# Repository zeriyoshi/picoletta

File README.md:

# picoletta
Jashin-chan Dropkick Open source Tenkey Macropad (formerly JCDK21)

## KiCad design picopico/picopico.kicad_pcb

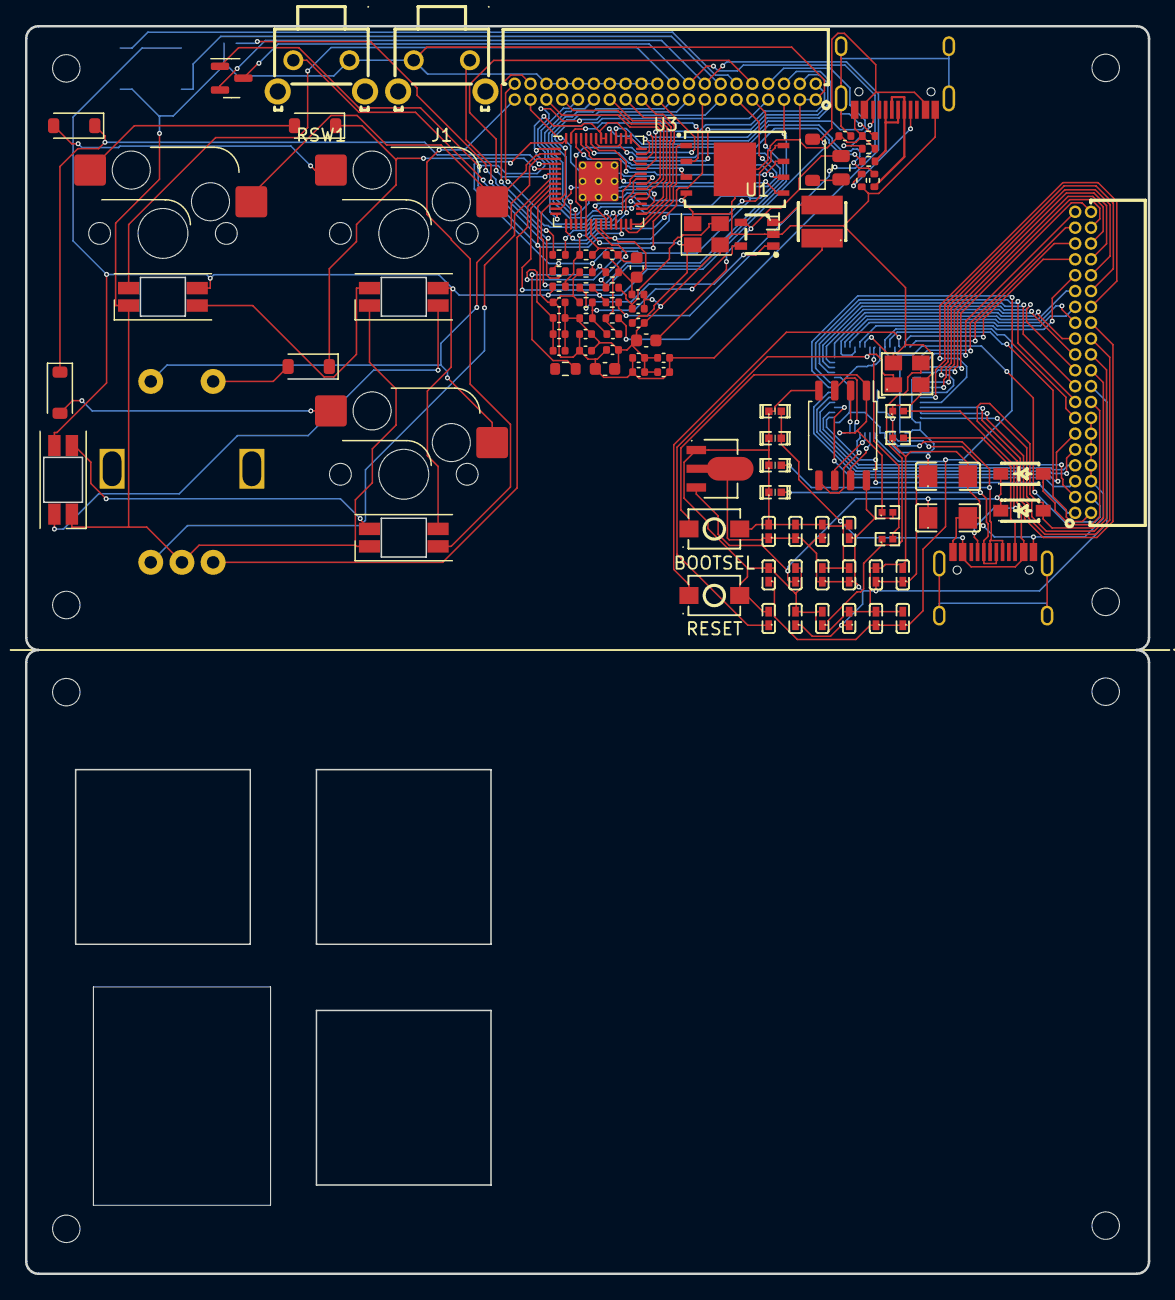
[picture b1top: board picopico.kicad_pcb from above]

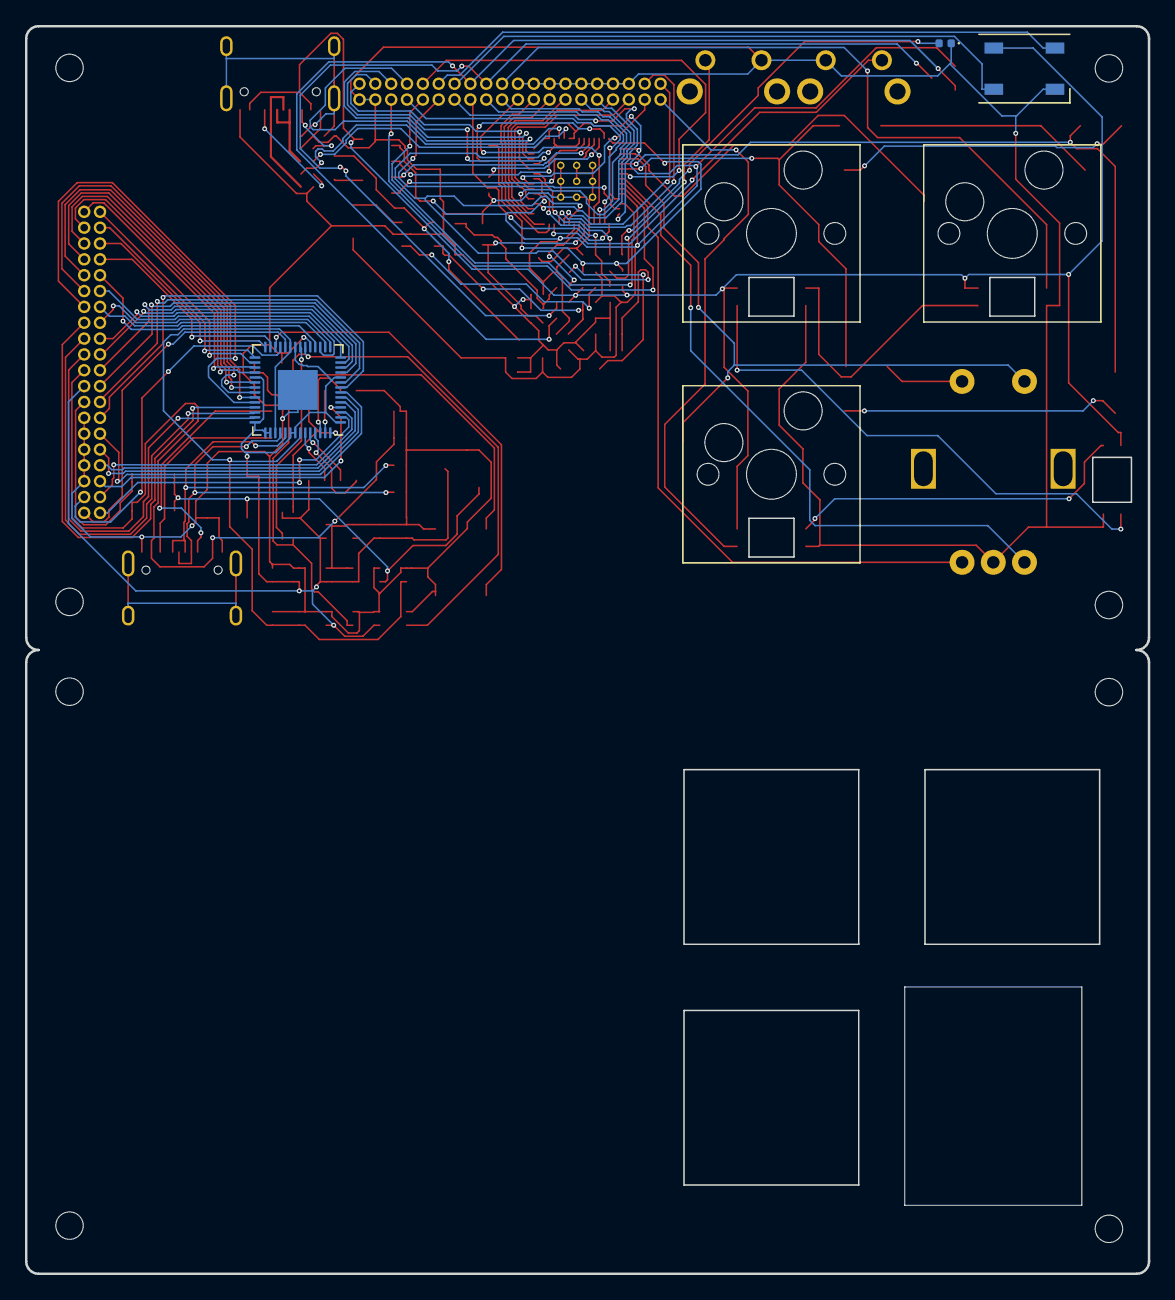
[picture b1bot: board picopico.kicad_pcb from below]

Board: 2 copper layers, 90.0 x 100.0 mm, 114 parts (9 on the bottom side), 125 nets.

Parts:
C1: 0.1uf 0402; C_0402_1005Metric
C2: 10uf 0402; C_0603_1608Metric
C3, C5, C6, C10, C12, C13, C14, C15, C16, C17, C18: 100nf 0402; C_0402_1005Metric
C4, C9: 10uf 0603; C_0603_1608Metric
C7, C11: 1uf 0402; C_0402_1005Metric
C8: 22pF; C_0402_1005Metric
C19, C20: 22pf 0402; C_0402_1005Metric
D1: 1N4002W; D_SOD-123
D2, D3, D4, D5: 1N1418W; D_SOD-123
D6: WS2812B; LED_WS2812B_PLCC4_5.0x5.0mm_P3.2mm
D7, D8, D9, D10: 0402ESDA-05N; D0402-BI
F1: 0805L050WR; Fuse_0805_2012Metric
FLASH1: W25Q16JVUXIQ; SON127P800X600X80-9N
G1, G2: LOGO; zeriparrot
GPIO25_LED1: LED_0402; LED_0402_1005Metric
GPIO25_RESISTOR1: 470 0402; R_0402_1005Metric
H1, H2, H3, H4, H5, H6, H7, H8: MountingHole; MountingHole_2.2mm_M2
H9, H10, H12: Switch_Hole
H11: RotaryEncoder_EC11-Hole
J1: 1-1825027-7; SW-TH_KH-6X6X4.3H-ZJ
L1: SWPA3015S2R2NT; IND-SMD_L3.0-W3.0
LED1, LED2, LED3, LED4: YS-SK6812MINI-E
Q1: BSS138; SOT-23
R1, R2: 5.1K 0402; R_0402_1005Metric
R3: 220 0402; R_0402_1005Metric
R4, R15: 1K 0402; R_0402_1005Metric
R5: 5.6K 0402; R_0402_1005Metric
R6, R7, R16, R17: 10K 0402; R_0402_1005Metric
R8: 100K 0402; R_0402_1005Metric
R9: 680K; R_0402_1005Metric
R10: 150K; R_0402_1005Metric
R11, R12: 27r 0402 resistor; R_0402_1005Metric
R13: 200 0603; R_0603_1608Metric
R14: 1 0402; R_0402_1005Metric
R19, R20: 0402WGF5101TCE; R0402
RSW1: 1-1825027-7; SW-TH_KH-6X6X4.3H-ZJ
SW1, SW2, SW3: SW_PUSH; SW_Hotswap_Kailh_MX_1.00u
SW4: RotaryEncoder_Switch; RotaryEncoder_EC11-Switch
U1: TD6810; SOT-23-5_L3.0-W1.7-P0.95-LS2.8-BR
U2: RP2040; RP2040-QFN-56
U3, U5: X1321FR-2X20-C43D24; CONN-TH_40P_X1321FR-2X20-C43D24
USB1, USB2: TYPE-C-31-M-12; HRO-TYPE-C-31-M-12
XTRAPI_C1, XTRAPI_C3: 0402CG300J500NT; C0402
XTRAPI_C2, XTRAPI_C5, XTRAPI_C6, XTRAPI_C7, XTRAPI_C8, XTRAPI_C9, XTRAPI_C10, XTRAPI_C11, XTRAPI_C12, XTRAPI_C13, XTRAPI_C15, XTRAPI_C16, XTRAPI_C17, XTRAPI_C18: CL05A106MQ5NUNC; C0402
XTRAPI_C4, XTRAPI_C14: CL31A107MQHNNNE; C1206
XTRAPI_R2: 0402WGF1002TCE; R0402
XTRAPI_R4: 0402WGF1001TCE; R0402
XTRAPI_U2: W25Q128JVS; SOIC-8_5.23x5.23mm_P1.27mm
XTRAPI_U3: RP2040; QFN-56-1EP_7x7mm_P0.4mm_EP3.2x3.2mm
XTRAPI_U4: AZ1117R-3_3TRE1; SOT-89-3_L4.5-W2.5-P1.50-LS4.2-BR
XTRAPI_U6, XTRAPI_U7: B5819W_C8598; SOD-123_L2.7-W1.6-LS3.7-RD-1
XTRAPI_X1: X322512MSB4SI; OSC-SMD_4P-L3.2-W2.5-BL
XTRA_SW_BOOTSEL1: TSA343G00-250J2; SW-SMD_L4.0-W2.9-LS5.0
XTRA_SW_RESET1: TSA343G00-250J2; SW-SMD_L4.0-W2.9-LS5.0
Y1: 3225_4P; Crystal_SMD_3225-4Pin_3.2x2.5mm

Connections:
3V3_EN: R8.1, U1.1 (RUN)
+1V1: C5.1, C6.1, C7.1, U2.23 (DVDD), U2.45 (VREG_VOUT), U2.50 (DVDD)
+3V3: C2.1, C3.1, C8.2, C9.1, C10.1, C11.1, C12.1, C13.1, C14.1, C15.1, C16.1, C17.1, C18.1, FLASH1.8 (VCC), L1.2, Q1.1 (G), R7.1, R9.1, R14.2, R17.1, U2.1 (IOVDD), U2.10 (IOVDD), U2.22 (IOVDD), U2.33 (IOVDD), U2.42 (IOVDD), U2.43 (ADC_AVDD), U2.44 (VREG_IN), U2.48 (USB_VDD), U2.49 (IOVDD)
/ADC_VREF: R13.2, R14.1
/D+: R11.2, U2.47 (USB_DP)
/D-: R12.2, U2.46 (USB_DM)
/GPIO7: U2.9 (GPIO7), U3.5
/GPIO8: U2.11 (GPIO8), U3.7
/GPIO9: U2.12 (GPIO9), U3.9
/GPIO10: U2.13 (GPIO10), U3.11
/GPIO11: U2.14 (GPIO11), U3.13
/GPIO12: U2.15 (GPIO12), U3.15
/GPIO13: U2.16 (GPIO13), U3.17
/GPIO14: U2.17 (GPIO14), U3.19
/GPIO15: U2.18 (GPIO15), U3.21
/GPIO16: U2.27 (GPIO16), U3.23
/GPIO17: U2.28 (GPIO17), U3.25
/GPIO18: U2.29 (GPIO18), U3.27
/GPIO19: U2.30 (GPIO19), U3.29
/GPIO20: U2.31 (GPIO20), U3.31
/GPIO21: U2.32 (GPIO21), U3.33
/GPIO22: U2.34 (GPIO22), U3.35
/GPIO23: U2.35 (GPIO23), U3.37
/GPIO24: R5.2, R6.1, U2.36 (GPIO24)
/GPIO25: GPIO25_RESISTOR1.2, U2.37 (GPIO25)
/GPIO26_ADC0: U2.38 (GPIO26_ADC0), U3.2
/GPIO27_ADC1: U2.39 (GPIO27_ADC1), U3.4
/GPIO28_ADC2: U2.40 (GPIO28_ADC2), U3.6
/GPIO29_ADC3: U2.41 (GPIO29_ADC3), U3.8
/QSPI_SCLK: FLASH1.6 (CLK), U2.52 (QSPI_SCLK)
/QSPI_SD0: FLASH1.5 (DI(IO0)), U2.53 (QSPI_SD0)
/QSPI_SD1: FLASH1.2 (DO(IO1)), U2.55 (QSPI_SD1)
/QSPI_SD2: FLASH1.3 (IO2), U2.54 (QSPI_SD2)
/QSPI_SD3: FLASH1.7 (IO3), U2.51 (QSPI_SD3)
/QSPI_SS: FLASH1.1 (~CS), R4.1, R7.2, U2.56 (QSPI_SS)
/RGB0: U2.6 (GPIO4), U3.10
/RGB0IN: LED1.4 (DIN), U3.20
/RGB0MOSFETIN: Q1.2 (S), R17.2, U3.16
/RGB0MOSFETOUT: Q1.3 (D), R16.2, U3.18
/RGB0OUT: LED4.2 (DOUT), U3.39
/RGB0WSIN: D6.4 (DIN), U3.12
/RGB0WSOUT: D6.2 (DOUT), U3.14
/RUN: RSW1.2, U2.26 (RUN)
/SWCLK: U2.24 (SWCLK), U3.40
/SWD: U2.25 (SWD), U3.38
/XP_+3V3: U5.18, XTRAPI_C2.1, XTRAPI_C4.1, XTRAPI_C5.1, XTRAPI_C10.1, XTRAPI_C11.1, XTRAPI_C12.1, XTRAPI_C13.1, XTRAPI_C15.1, XTRAPI_C16.1, XTRAPI_C17.1, XTRAPI_C18.1, XTRAPI_R2.2, XTRAPI_U2.8 (VCC), XTRAPI_U3.1 (IOVDD), XTRAPI_U3.10 (IOVDD), XTRAPI_U3.22 (IOVDD), XTRAPI_U3.33 (IOVDD), XTRAPI_U3.42 (IOVDD), XTRAPI_U3.43 (ADC_AVDD), XTRAPI_U3.44 (VREG_IN), XTRAPI_U3.48 (USB_VDD), XTRAPI_U3.49 (IOVDD), XTRAPI_U4.2 (OUTPUT)
/XP_BOOTSEL: XTRAPI_R2.1, XTRAPI_U2.1 (~CS), XTRAPI_U3.56 (QSPI_SS), XTRA_SW_BOOTSEL1.1
/XP_GPIO0: U5.1, XTRAPI_U3.2 (GPIO0)
/XP_GPIO1: U5.3, XTRAPI_U3.3 (GPIO1)
/XP_GPIO2: U5.5, XTRAPI_U3.4 (GPIO2)
/XP_GPIO3: U5.7, XTRAPI_U3.5 (GPIO3)
/XP_GPIO4: U5.9, XTRAPI_U3.6 (GPIO4)
/XP_GPIO5: U5.11, XTRAPI_U3.7 (GPIO5)
/XP_GPIO6: U5.13, XTRAPI_U3.8 (GPIO6)
/XP_GPIO7: U5.15, XTRAPI_U3.9 (GPIO7)
/XP_GPIO8: U5.17, XTRAPI_U3.11 (GPIO8)
/XP_GPIO9: U5.19, XTRAPI_U3.12 (GPIO9)
/XP_GPIO10: U5.21, XTRAPI_U3.13 (GPIO10)
/XP_GPIO11: U5.23, XTRAPI_U3.14 (GPIO11)
/XP_GPIO12: U5.25, XTRAPI_U3.15 (GPIO12)
/XP_GPIO13: U5.27, XTRAPI_U3.16 (GPIO13)
/XP_GPIO14: U5.29, XTRAPI_U3.17 (GPIO14)
/XP_GPIO15: U5.31, XTRAPI_U3.18 (GPIO15)
/XP_GPIO16: U5.33, XTRAPI_U3.27 (GPIO16)
/XP_GPIO17: U5.35, XTRAPI_U3.28 (GPIO17)
/XP_GPIO18: U5.37, XTRAPI_U3.29 (GPIO18)
/XP_GPIO19: U5.39, XTRAPI_U3.30 (GPIO19)
/XP_GPIO20: U5.40, XTRAPI_U3.31 (GPIO20)
/XP_GPIO21: U5.38, XTRAPI_U3.32 (GPIO21)
/XP_GPIO22: U5.36, XTRAPI_U3.34 (GPIO22)
/XP_GPIO23: U5.34, XTRAPI_U3.35 (GPIO23)
/XP_GPIO24: U5.32, XTRAPI_U3.36 (GPIO24)
/XP_GPIO25: U5.30, XTRAPI_U3.37 (GPIO25)
/XP_GPIO26_ADC0: U5.28, XTRAPI_U3.38 (GPIO26_ADC0)
/XP_GPIO27_ADC1: U5.26, XTRAPI_U3.39 (GPIO27_ADC1)
/XP_GPIO28_ADC2: U5.24, XTRAPI_U3.40 (GPIO28_ADC2)
/XP_GPIO29_ADC3: U5.22, XTRAPI_U3.41 (GPIO29_ADC3)
/XP_RUN: XTRAPI_U3.26 (RUN), XTRA_SW_RESET1.1
/XP_SWCLK: U5.2, XTRAPI_U3.24 (SWCLK)
/XP_SWD: U5.4, XTRAPI_U3.25 (SWD)
/XP_USB_DN: D10.2, USB2.5 (DN2), USB2.7 (DN1), XTRAPI_U3.46 (USB_DM)
/XP_USB_DP: D9.2, USB2.6 (DP1), USB2.8 (DP2), XTRAPI_U3.47 (USB_DP)
/XP_VBUS: D7.2, D8.2, U5.20, USB2.2 (VBUS), USB2.11 (VBUS), XTRAPI_U7.2 (+)
/XP_VSYS: U5.16, XTRAPI_U6.2 (+)
/~USB_BOOT: J1.1, R4.2
COL0: SW1.1, SW2.1, U2.2 (GPIO0)
COL1: SW3.1, SW4.S2, U2.3 (GPIO1)
GND: C1.1, C2.2, C3.2, C4.2, C5.2, C6.2, C7.2, C9.2, C10.2, C11.2, C12.2, C13.2, C14.2, C15.2, C16.2, C17.2, C18.2, C19.1, C20.1, D6.3 (VSS), D7.1, D8.1, D9.1, D10.1, FLASH1.4 (GND), FLASH1.9 (EXP), GPIO25_LED1.1 (K), J1.2, LED1.3 (VSS), LED2.3 (VSS), LED3.3 (VSS), LED4.3 (VSS), R1.1, R2.1, R3.2, R6.2, R10.1, R19.1, R20.1, RSW1.1, SW4.C, U1.2 (GND), U2.19 (TESTEN), U2.57 (GND), U3.1, U3.3, U3.22, U3.24, U3.26, U3.28, U3.30, U3.32, U3.34, U3.36, U5.6, U5.8, U5.10, U5.12, U5.14, USB1.1 (GND), USB1.12 (GND), USB2.1 (GND), USB2.12 (GND), XTRAPI_C1.2, XTRAPI_C2.2, XTRAPI_C3.2, XTRAPI_C4.2, XTRAPI_C5.2, XTRAPI_C6.2, XTRAPI_C7.2, XTRAPI_C8.2, XTRAPI_C9.2, XTRAPI_C10.2, XTRAPI_C11.2, XTRAPI_C12.2, XTRAPI_C13.2, XTRAPI_C14.2, XTRAPI_C15.2, XTRAPI_C16.2, XTRAPI_C17.2, XTRAPI_C18.2, XTRAPI_U2.4 (GND), XTRAPI_U3.19 (TESTEN), XTRAPI_U3.57 (GND), XTRAPI_U4.1 (ADJ/GND), XTRAPI_X1.2 (GND), XTRAPI_X1.4 (GND), XTRA_SW_BOOTSEL1.2, XTRA_SW_RESET1.2, Y1.2, Y1.4
unnamed: C20.2, R15.2, Y1.3
unnamed: D2.2 (A), SW1.2
unnamed: D3.2 (A), SW2.2
unnamed: D4.2 (A), SW3.2
unnamed: D5.2 (A), SW4.S1
unnamed: GPIO25_LED1.2 (A), GPIO25_RESISTOR1.1
unnamed: LED1.2 (DOUT), LED2.4 (DIN)
unnamed: LED2.2 (DOUT), LED3.4 (DIN)
unnamed: LED3.2 (DOUT), LED4.4 (DIN)
unnamed: L1.1, U1.3 (SW)
unnamed: C8.1, R9.2, R10.2, U1.5 (VFB/VOUT)
unnamed: C4.1, F1.1, U1.4 (VIN)
unnamed: R1.2, USB1.4 (CC1)
unnamed: R2.2, USB1.10 (CC2)
unnamed: C1.2, R3.1, USB1.13 (SHIELD)
unnamed: R19.2, USB2.4 (CC1)
unnamed: R20.2, USB2.10 (CC2)
unnamed: XTRAPI_U2.6 (CLK), XTRAPI_U3.52 (QSPI_SCLK)
unnamed: XTRAPI_U2.5 (DI(IO0)), XTRAPI_U3.53 (QSPI_SD0)
unnamed: XTRAPI_U2.2 (DO(IO1)), XTRAPI_U3.55 (QSPI_SD1)
unnamed: XTRAPI_U2.3 (IO2), XTRAPI_U3.54 (QSPI_SD2)
unnamed: XTRAPI_U2.7 (IO3), XTRAPI_U3.51 (QSPI_SD3)
unnamed: XTRAPI_C6.1, XTRAPI_C7.1, XTRAPI_C8.1, XTRAPI_U3.23 (DVDD), XTRAPI_U3.45 (VREG_VOUT), XTRAPI_U3.50 (DVDD)
unnamed: XTRAPI_C1.1, XTRAPI_U3.20 (XIN), XTRAPI_X1.1 (OSC1)
unnamed: XTRAPI_R4.2, XTRAPI_U3.21 (XOUT)
unnamed: XTRAPI_C9.1, XTRAPI_C14.1, XTRAPI_U4.3 (INPUT), XTRAPI_U6.1 (-), XTRAPI_U7.1 (-)
unnamed: XTRAPI_C3.1, XTRAPI_R4.1, XTRAPI_X1.3 (OSC2)
ROT0IN: SW4.B, U2.7 (GPIO5)
ROT0OUT: SW4.A, U2.8 (GPIO6)
ROW0: D2.1 (K), D4.1 (K), U2.4 (GPIO2)
ROW1: D3.1 (K), D5.1 (K), U2.5 (GPIO3)
USB_D+: R11.1, USB1.6 (DP1), USB1.8 (DP2)
USB_D-: R12.1, USB1.5 (DN2), USB1.7 (DN1)
VBUS: D1.2 (A), D6.1 (VDD), LED1.1 (VDD), LED2.1 (VDD), LED3.1 (VDD), LED4.1 (VDD), R5.1, R8.2, R16.1, USB1.2 (VBUS), USB1.11 (VBUS)
VSYS: D1.1 (K), F1.2
XIN: C19.2, U2.20 (XIN), Y1.1
XOUT: R15.1, U2.21 (XOUT)

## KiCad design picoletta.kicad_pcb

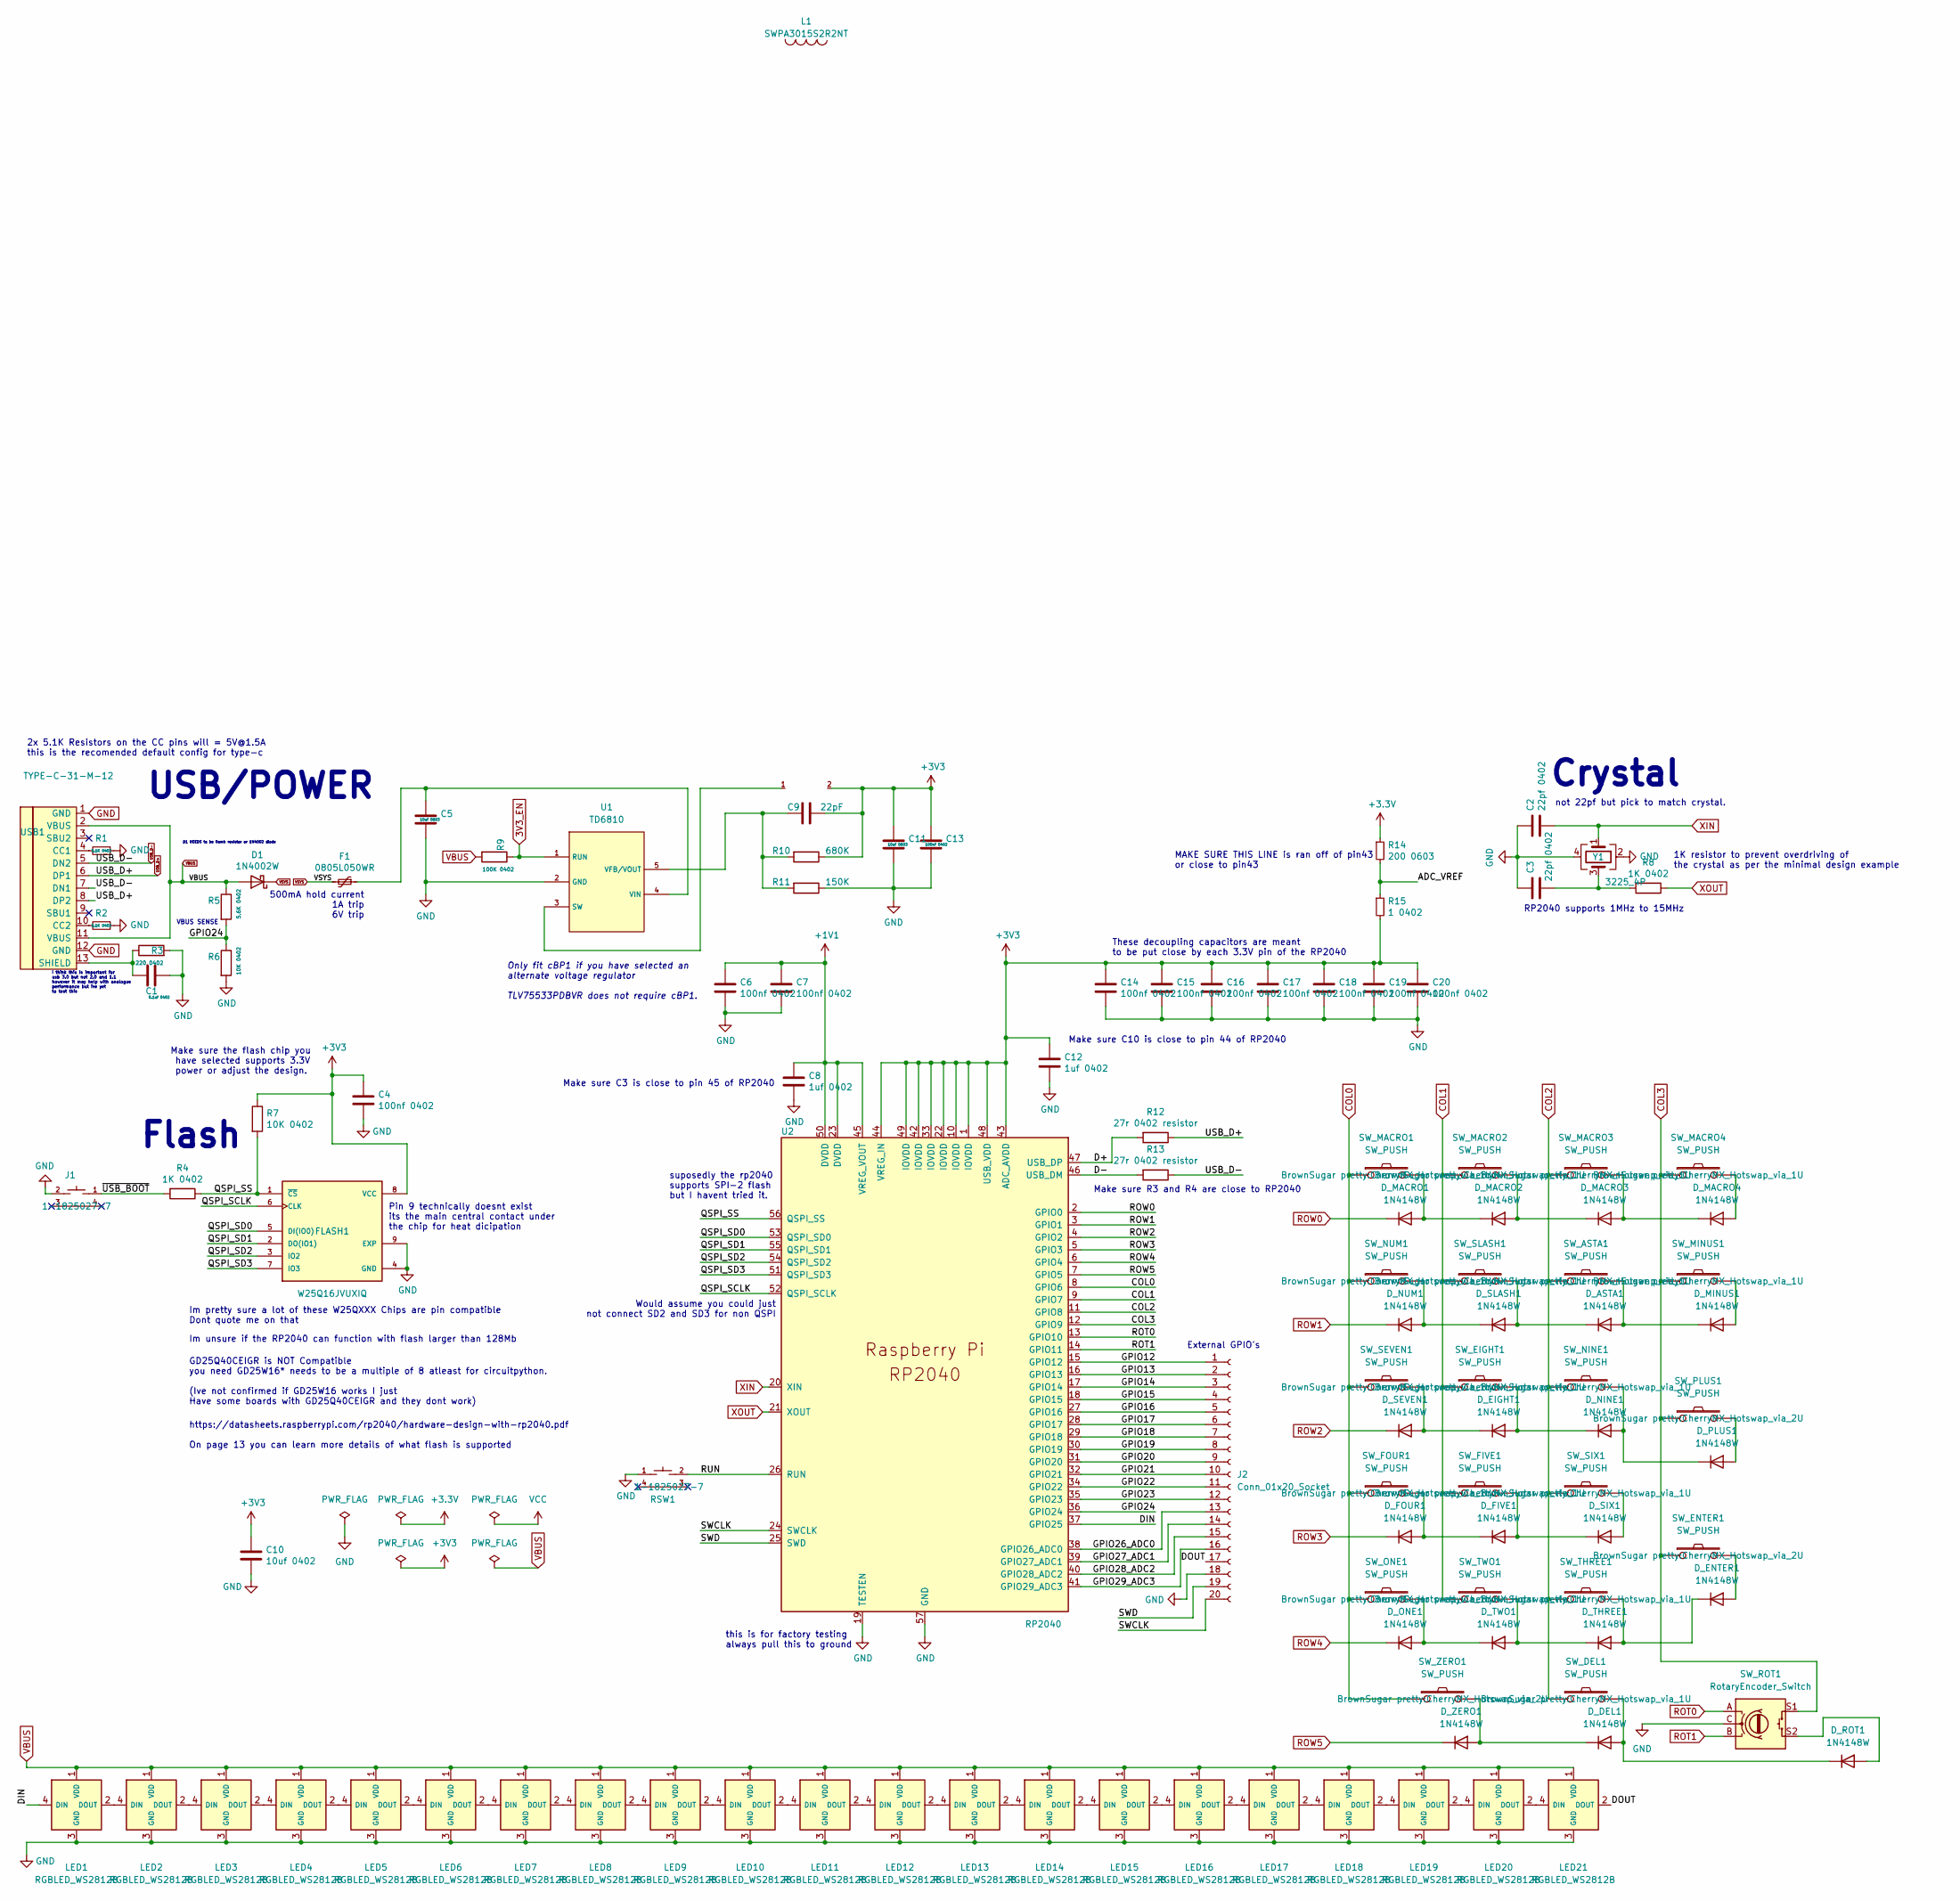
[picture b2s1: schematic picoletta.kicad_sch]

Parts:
C1: 0.1uf 0402; C_0402_1005Metric
C2, C3: 22pf 0402; C_0402_1005Metric
C4, C6, C7, C13, C14, C15, C16, C17, C18, C19, C20: 100nf 0402; C_0402_1005Metric
C5, C11: 10uf 0603; C_0603_1608Metric
C8, C12: 1uf 0402; C_0402_1005Metric
C9: 22pF; C_0402_1005Metric
C10: 10uf 0402; C_0603_1608Metric
D1: 1N4002W; D_SOD-123
D_ASTA1: 1N4148W; D_SOD-123
D_DEL1: 1N4148W; D_SOD-123
D_EIGHT1: 1N4148W; D_SOD-123
D_ENTER1: 1N4148W; D_SOD-123
D_FIVE1: 1N4148W; D_SOD-123
D_FOUR1: 1N4148W; D_SOD-123
D_MACRO1, D_MACRO2, D_MACRO3, D_MACRO4: 1N4148W; D_SOD-123
D_MINUS1: 1N4148W; D_SOD-123
D_NINE1: 1N4148W; D_SOD-123
D_NUM1: 1N4148W; D_SOD-123
D_ONE1: 1N4148W; D_SOD-123
D_PLUS1: 1N4148W; D_SOD-123
D_ROT1: 1N4148W; D_SOD-123
D_SEVEN1: 1N4148W; D_SOD-123
D_SIX1: 1N4148W; D_SOD-123
D_SLASH1: 1N4148W; D_SOD-123
D_THREE1: 1N4148W; D_SOD-123
D_TWO1: 1N4148W; D_SOD-123
D_ZERO1: 1N4148W; D_SOD-123
F1: 0805L050WR; Fuse_0805_2012Metric
FLASH1: W25Q16JVUXIQ; SON127P800X600X80-9N
J1: 1-1825027-7; SW-TH_KH-6X6X4.3H-ZJ; LCSC C592923
J2: Conn_01x20_Socket; PinSocket_1x20_P2.54mm_Horizontal
L1: SWPA3015S2R2NT; IND-SMD_L3.0-W3.0; LCSC C19734
LED1: RGBLED_WS2812B; RGBLED_SK6812MINI-E
LED2, LED3, LED4, LED5, LED6, LED7, LED8, LED9, LED10, LED11, LED12, LED13, LED14, LED15, LED16, LED17, LED18, LED19, LED20, LED21: RGBLED_WS2812B
R1, R2: 5.1K 0402; R_0402_1005Metric
R3: 220 0402; R_0402_1005Metric
R4, R8: 1K 0402; R_0402_1005Metric
R5: 5.6K 0402; R_0402_1005Metric
R6, R7: 10K 0402; R_0402_1005Metric
R9: 100K 0402; R_0402_1005Metric
R10: 680K; R_0402_1005Metric
R11: 150K; R_0402_1005Metric
R12, R13: 27r 0402 resistor; R_0402_1005Metric
R14: 200 0603; R_0603_1608Metric
R15: 1 0402; R_0402_1005Metric
RSW1: 1-1825027-7; SW-TH_KH-6X6X4.3H-ZJ; LCSC C592923
SW_ASTA1: SW_PUSH; CherryMX_Hotswap_via_1U
SW_DEL1: SW_PUSH; CherryMX_Hotswap_via_1U
SW_EIGHT1: SW_PUSH; CherryMX_Hotswap_via_1U
SW_ENTER1: SW_PUSH; CherryMX_Hotswap_via_2U
SW_FIVE1: SW_PUSH; CherryMX_Hotswap_via_1U
SW_FOUR1: SW_PUSH; CherryMX_Hotswap_via_1U
SW_MACRO1, SW_MACRO2, SW_MACRO3, SW_MACRO4: SW_PUSH; CherryMX_Hotswap_via_1U
SW_MINUS1: SW_PUSH; CherryMX_Hotswap_via_1U
SW_NINE1: SW_PUSH; CherryMX_Hotswap_via_1U
SW_NUM1: SW_PUSH; CherryMX_Hotswap_via_1U
SW_ONE1: SW_PUSH; CherryMX_Hotswap_via_1U
SW_PLUS1: SW_PUSH; CherryMX_Hotswap_via_2U
SW_ROT1: RotaryEncoder_Switch; RotaryEncoder_EC11-Switch
SW_SEVEN1: SW_PUSH; CherryMX_Hotswap_via_1U
SW_SIX1: SW_PUSH; CherryMX_Hotswap_via_1U
SW_SLASH1: SW_PUSH; CherryMX_Hotswap_via_1U
SW_THREE1: SW_PUSH; CherryMX_Hotswap_via_1U
SW_TWO1: SW_PUSH; CherryMX_Hotswap_via_1U
SW_ZERO1: SW_PUSH; CherryMX_Hotswap_via_2U
U1: TD6810; SOT-23-5_L3.0-W1.7-P0.95-LS2.8-BR; LCSC C16510
U2: RP2040; RP2040-QFN-56; LCSC C2040
USB1: TYPE-C-31-M-12; HRO-TYPE-C-31-M-12
Y1: 3225_4P; Crystal_SMD_3225-4Pin_3.2x2.5mm

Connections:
3V3_EN: R9.1, U1.1 (RUN)
+1V1: C6.1, C7.1, C8.1, U2.23 (DVDD), U2.45 (VREG_VOUT), U2.50 (DVDD)
+3.3V: R14.1
+3V3: C4.1, C9.2, C10.1, C11.1, C12.1, C13.1, C14.1, C15.1, C16.1, C17.1, C18.1, C19.1, C20.1, FLASH1.8 (VCC), L1.2, R7.1, R10.1, R15.2, U2.1 (IOVDD), U2.10 (IOVDD), U2.22 (IOVDD), U2.33 (IOVDD), U2.42 (IOVDD), U2.43 (ADC_AVDD), U2.44 (VREG_IN), U2.48 (USB_VDD), U2.49 (IOVDD)
/ADC_VREF: R14.2, R15.1
/D+: R12.2, U2.47 (USB_DP)
/D-: R13.2, U2.46 (USB_DM)
/DIN: LED1.4 (DIN), U2.37 (GPIO25)
/DOUT: J2.17, LED21.2 (DOUT)
/GPIO12: J2.1, U2.15 (GPIO12)
/GPIO13: J2.2, U2.16 (GPIO13)
/GPIO14: J2.3, U2.17 (GPIO14)
/GPIO15: J2.4, U2.18 (GPIO15)
/GPIO16: J2.5, U2.27 (GPIO16)
/GPIO17: J2.6, U2.28 (GPIO17)
/GPIO18: J2.7, U2.29 (GPIO18)
/GPIO19: J2.8, U2.30 (GPIO19)
/GPIO20: J2.9, U2.31 (GPIO20)
/GPIO21: J2.10, U2.32 (GPIO21)
/GPIO22: J2.11, U2.34 (GPIO22)
/GPIO23: J2.12, U2.35 (GPIO23)
/GPIO24: R5.2, R6.1, U2.36 (GPIO24)
/GPIO26_ADC0: J2.13, U2.38 (GPIO26_ADC0)
/GPIO27_ADC1: J2.14, U2.39 (GPIO27_ADC1)
/GPIO28_ADC2: J2.15, U2.40 (GPIO28_ADC2)
/GPIO29_ADC3: J2.16, U2.41 (GPIO29_ADC3)
/QSPI_SCLK: FLASH1.6 (CLK), U2.52 (QSPI_SCLK)
/QSPI_SD0: FLASH1.5 (DI(IO0)), U2.53 (QSPI_SD0)
/QSPI_SD1: FLASH1.2 (DO(IO1)), U2.55 (QSPI_SD1)
/QSPI_SD2: FLASH1.3 (IO2), U2.54 (QSPI_SD2)
/QSPI_SD3: FLASH1.7 (IO3), U2.51 (QSPI_SD3)
/QSPI_SS: FLASH1.1 (~CS), R4.1, R7.2, U2.56 (QSPI_SS)
/RUN: RSW1.2, U2.26 (RUN)
/SWCLK: J2.20, U2.24 (SWCLK)
/SWD: J2.19, U2.25 (SWD)
/~USB_BOOT: J1.1, R4.2
COL0: SW_FOUR1.1, SW_MACRO1.1, SW_NUM1.1, SW_ONE1.1, SW_SEVEN1.1, SW_ZERO1.1, U2.8 (GPIO6)
COL1: SW_EIGHT1.1, SW_FIVE1.1, SW_MACRO2.1, SW_SLASH1.1, SW_TWO1.1, U2.9 (GPIO7)
COL2: SW_ASTA1.1, SW_DEL1.1, SW_MACRO3.1, SW_NINE1.1, SW_SIX1.1, SW_THREE1.1, U2.11 (GPIO8)
COL3: SW_ENTER1.1, SW_MACRO4.1, SW_MINUS1.1, SW_PLUS1.1, SW_ROT1.S1, U2.12 (GPIO9)
GND: C1.1, C2.1, C3.1, C4.2, C5.2, C6.2, C7.2, C8.2, C10.2, C11.2, C12.2, C13.2, C14.2, C15.2, C16.2, C17.2, C18.2, C19.2, C20.2, FLASH1.4 (GND), FLASH1.9 (EXP), J1.2, J2.18, LED1.3 (GND), LED2.3 (GND), LED3.3 (GND), LED4.3 (GND), LED5.3 (GND), LED6.3 (GND), LED7.3 (GND), LED8.3 (GND), LED9.3 (GND), LED10.3 (GND), LED11.3 (GND), LED12.3 (GND), LED13.3 (GND), LED14.3 (GND), LED15.3 (GND), LED16.3 (GND), LED17.3 (GND), LED18.3 (GND), LED19.3 (GND), LED20.3 (GND), LED21.3 (GND), R1.1, R2.1, R3.2, R6.2, R11.1, RSW1.1, SW_ROT1.C, U1.2 (GND), U2.19 (TESTEN), U2.57 (GND), USB1.1 (GND), USB1.12 (GND), Y1.2, Y1.4
unnamed: C3.2, R8.2, Y1.3
unnamed: D_ASTA1.2 (A), D_MINUS1.1 (K), SW_ASTA1.2
unnamed: D_ASTA1.1 (K), D_SLASH1.2 (A), SW_SLASH1.2
unnamed: D_DEL1.2 (A), D_ROT1.1 (K), SW_DEL1.2
unnamed: D_DEL1.1 (K), D_ZERO1.2 (A), SW_ZERO1.2
unnamed: D_EIGHT1.2 (A), D_NINE1.1 (K), SW_EIGHT1.2
unnamed: D_EIGHT1.1 (K), D_SEVEN1.2 (A), SW_SEVEN1.2
unnamed: D_ENTER1.2 (A), SW_ENTER1.2
unnamed: D_ENTER1.1 (K), D_THREE1.2 (A), SW_THREE1.2
unnamed: D_FIVE1.2 (A), D_SIX1.1 (K), SW_FIVE1.2
unnamed: D_FIVE1.1 (K), D_FOUR1.2 (A), SW_FOUR1.2
unnamed: D_MACRO1.2 (A), D_MACRO2.1 (K), SW_MACRO1.2
unnamed: D_MACRO2.2 (A), D_MACRO3.1 (K), SW_MACRO2.2
unnamed: D_MACRO3.2 (A), D_MACRO4.1 (K), SW_MACRO3.2
unnamed: D_MACRO4.2 (A), SW_MACRO4.2
unnamed: D_MINUS1.2 (A), SW_MINUS1.2
unnamed: D_NINE1.2 (A), D_PLUS1.1 (K), SW_NINE1.2
unnamed: D_NUM1.2 (A), D_SLASH1.1 (K), SW_NUM1.2
unnamed: D_ONE1.2 (A), D_TWO1.1 (K), SW_ONE1.2
unnamed: D_PLUS1.2 (A), SW_PLUS1.2
unnamed: D_ROT1.2 (A), SW_ROT1.S2
unnamed: D_SIX1.2 (A), SW_SIX1.2
unnamed: D_THREE1.1 (K), D_TWO1.2 (A), SW_TWO1.2
unnamed: LED1.2 (DOUT), LED2.4 (DIN)
unnamed: LED2.2 (DOUT), LED3.4 (DIN)
unnamed: LED3.2 (DOUT), LED4.4 (DIN)
unnamed: LED4.2 (DOUT), LED5.4 (DIN)
unnamed: LED5.2 (DOUT), LED6.4 (DIN)
unnamed: LED6.2 (DOUT), LED7.4 (DIN)
unnamed: LED7.2 (DOUT), LED8.4 (DIN)
unnamed: LED8.2 (DOUT), LED9.4 (DIN)
unnamed: LED9.2 (DOUT), LED10.4 (DIN)
unnamed: LED10.2 (DOUT), LED11.4 (DIN)
unnamed: LED11.2 (DOUT), LED12.4 (DIN)
unnamed: LED12.2 (DOUT), LED13.4 (DIN)
unnamed: LED13.2 (DOUT), LED14.4 (DIN)
unnamed: LED14.2 (DOUT), LED15.4 (DIN)
unnamed: LED15.2 (DOUT), LED16.4 (DIN)
unnamed: LED16.2 (DOUT), LED17.4 (DIN)
unnamed: LED17.2 (DOUT), LED18.4 (DIN)
unnamed: LED18.2 (DOUT), LED19.4 (DIN)
unnamed: LED19.2 (DOUT), LED20.4 (DIN)
unnamed: LED20.2 (DOUT), LED21.4 (DIN)
unnamed: L1.1, U1.3 (SW)
unnamed: C9.1, R10.2, R11.2, U1.5 (VFB/VOUT)
unnamed: C5.1, F1.1, U1.4 (VIN)
unnamed: R1.2, USB1.4 (CC1)
unnamed: R2.2, USB1.10 (CC2)
unnamed: C1.2, R3.1, USB1.13 (SHIELD)
ROT0: SW_ROT1.A, U2.13 (GPIO10)
ROT1: SW_ROT1.B, U2.14 (GPIO11)
ROW0: D_MACRO1.1 (K), U2.2 (GPIO0)
ROW1: D_NUM1.1 (K), U2.3 (GPIO1)
ROW2: D_SEVEN1.1 (K), U2.4 (GPIO2)
ROW3: D_FOUR1.1 (K), U2.5 (GPIO3)
ROW4: D_ONE1.1 (K), U2.6 (GPIO4)
ROW5: D_ZERO1.1 (K), U2.7 (GPIO5)
USB_D+: R12.1, USB1.6 (DP1), USB1.8 (DP2)
USB_D-: R13.1, USB1.5 (DN2), USB1.7 (DN1)
VBUS: D1.2 (A), LED1.1 (VDD), LED2.1 (VDD), LED3.1 (VDD), LED4.1 (VDD), LED5.1 (VDD), LED6.1 (VDD), LED7.1 (VDD), LED8.1 (VDD), LED9.1 (VDD), LED10.1 (VDD), LED11.1 (VDD), LED12.1 (VDD), LED13.1 (VDD), LED14.1 (VDD), LED15.1 (VDD), LED16.1 (VDD), LED17.1 (VDD), LED18.1 (VDD), LED19.1 (VDD), LED20.1 (VDD), LED21.1 (VDD), R5.1, R9.2, USB1.2 (VBUS), USB1.11 (VBUS)
VSYS: D1.1 (K), F1.2
XIN: C2.2, U2.20 (XIN), Y1.1
XOUT: R8.1, U2.21 (XOUT)

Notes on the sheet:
2x 5.1K Resistors on the CC pins will = 5V@1.5A this is the recomended default config for type-c
USB/POWER
1K resistor to prevent overdriving of the crystal as per the minimal design example
not 22pf but pick to match crystal.
Only fit cBP1 if you have selected an alternate voltage regulator TLV75533PDBVR does not require cBP1.
RP2040 supports 1MHz to 15MHz
Would assume you could just not connect SD2 and SD3 for non QSPI
MAKE SURE THIS LINE is ran off of pin43 or close to pin43
suposedly the rp2040 supports SPI-2 flash but I havent tried it.
These decoupling capacitors are meant to be put close by each 3.3V pin of the RP2040
Make sure C3 is close to pin 45 of RP2040
https://datasheets.raspberrypi.com/rp2040/hardware-design-with-rp2040.pdf On page 13 you can learn more details of what flash is supported
this is for factory testing always pull this to ground
VBUS SENSE
GD25Q40CEIGR is NOT Compatible you need GD25W16* needs to be a multiple of 8 atleast for circuitpython. (Ive not confirmed if GD25W16 works I just Have some boards with GD25Q40CEIGR and they dont work)
External GPIO's
Make sure the flash chip you have selected supports 3.3V power or adjust the design.
I think this is important for usb 3.0 but not 2.0 and 1.1 however it may help with analogue performance but ive yet to test this
Im pretty sure a lot of these W25QXXX Chips are pin compatible Dont quote me on that
Make sure C10 is close to pin 44 of RP2040
500mA hold current 1A trip 6V trip
Make sure R3 and R4 are close to RP2040
D1 NEEDS to be 0omh resistor or 1N4002 diode
Crystal
Im unsure if the RP2040 can function with flash larger than 128Mb
Pin 9 technically doesnt exist its the main central contact under the chip for heat dicipation
Flash

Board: 2 copper layers, 111 parts (0 on the bottom side), 103 nets, no tracks yet.
